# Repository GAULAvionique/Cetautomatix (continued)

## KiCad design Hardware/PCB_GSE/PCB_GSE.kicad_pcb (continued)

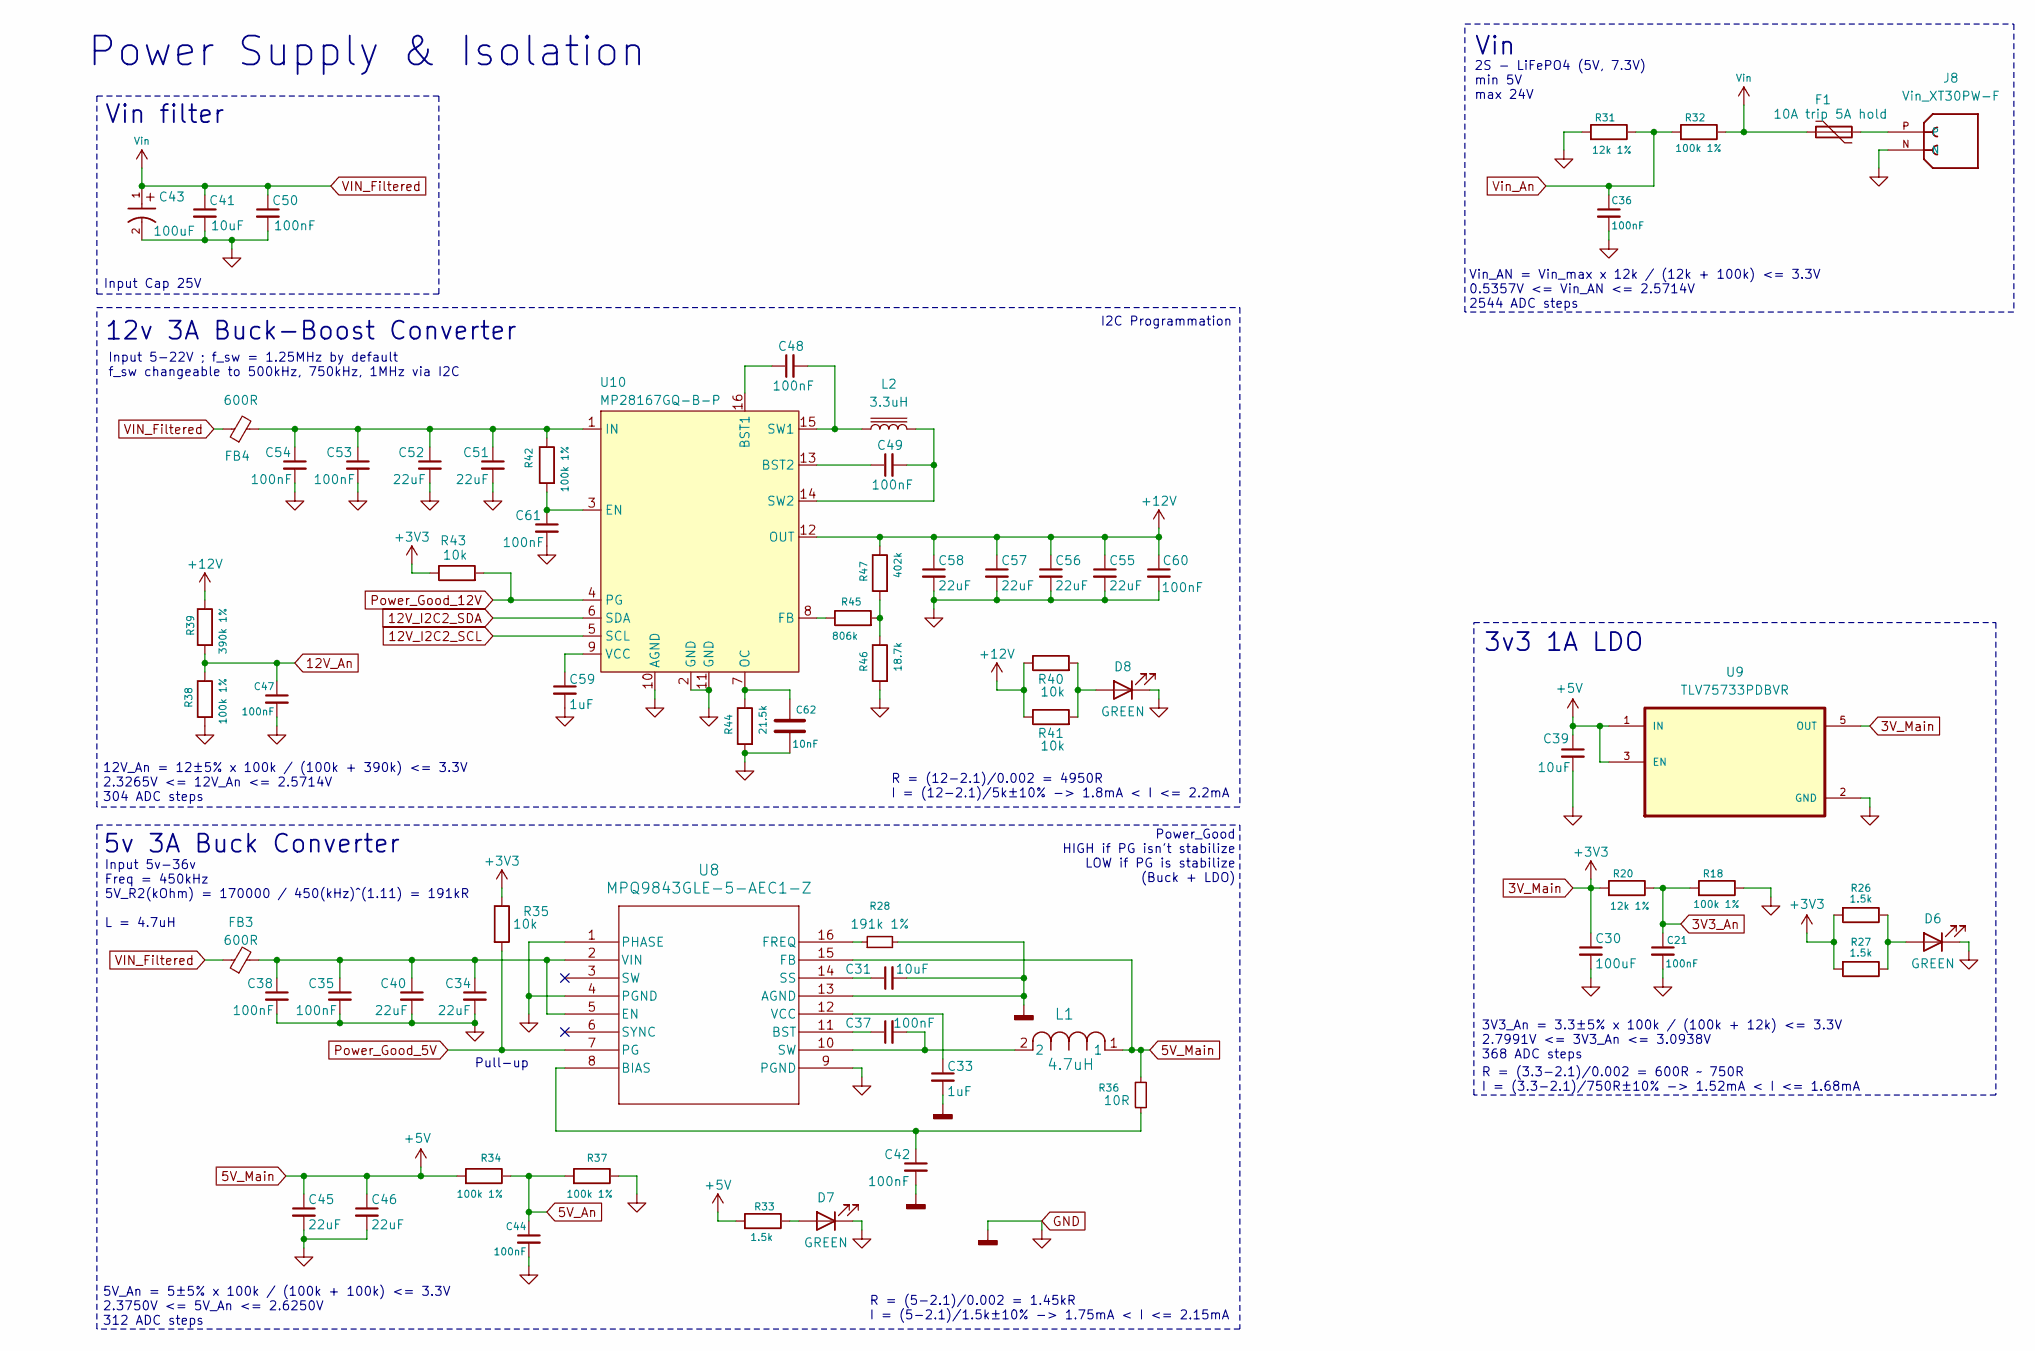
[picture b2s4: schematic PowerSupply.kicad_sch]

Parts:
C21, C35, C36, C37, C38, C42, C44, C47, C48, C49, C50, C53, C54, C60, C61: 100nF; C_0603_1608Metric; Manufacturer_Part_Number C0603C104K3RACTU; DigiKey_Part_Number 399-C0603C104K3RACTUCT-ND
C30: 100uF; C_1210_3225Metric; Manufacturer_Part_Number EMK325ABJ107MM-P; DigiKey_Part_Number 587-5426-1-ND
C31, C39, C41: 10uF; C_0805_2012Metric; Manufacturer_Part_Number CL21A106KAYNNNE; DigiKey_Part_Number 1276-2891-1-ND
C33, C59: 1uF; C_0805_2012Metric; Manufacturer_Part_Number CL21B105KBFNNNE; DigiKey_Part_Number 1276-1029-1-ND
C34, C40, C45, C46, C51, C52, C55, C56, C57, C58: 22uF; C_0805_2012Metric; Manufacturer_Part_Number C2012X5R1V226M125AC; DigiKey_Part_Number 445-14428-1-ND
C43: 100uF; U2-K_NCH; Manufacturer_Part_Number UCL1E101MCL1GS; DigiKey_Part_Number 493-3937-1-ND
C62: 10nF; C_0805_2012Metric; Manufacturer_Part_Number CL21B103KAANNNC; DigiKey_Part_Number 1276-2434-1-ND
D6, D7, D8: GREEN; LED_QBLP601-AG15; Manufacturer_Part_Number QBLP601-AG15; DigiKey_Part_Number 1516-QBLP601-AG15CT-ND
F1: 10A trip 5A hold; Fuse_2920_7451Metric; Manufacturer_Part_Number 2920L500/24SLDR; DigiKey_Part_Number 18-2920L500/24SLDRCT-ND
FB3, FB4: 600R; L_1210_3225Metric; Manufacturer_Part_Number FBMH3225HM601NT; DigiKey_Part_Number 587-1755-1-ND
J8: Vin_XT30PW-F; XT30PW-F; PARTREV 1.2
L1: 4.7uH; IND_PA4342_PUL; Manufacturer_Part_Number PA4342.472NLT; Digikey 553-3001-1-ND
L2: 3.3uH; MPL-AL6050-3R3; Manufacturer_Part_Number MPL-AL6050-3R3; DigiKey_Part_Number 1589-MPL-AL6050-3R3CT-ND
R18, R32, R34, R37, R38, R42: 100k 1%; R_0805_2012Metric; Manufacturer_Part_Number RC0805FR-07100KL; DigiKey_Part_Number 311-100KCRCT-ND
R20, R31: 12k 1%; R_0805_2012Metric; Manufacturer_Part_Number RC0805FR-0712KL; DigiKey_Part_Number 311-12.0KCRCT-ND
R26, R27, R33: 1.5k; R_0805_2012Metric; Manufacturer_Part_Number RC0805FR-071K5L; DigiKey_Part_Number 311-1.50KCRCT-ND
R28: 191k 1%; R_0805_2012Metric; Manufacturer_Part_Number RC0805FR-07191KL; DigiKey_Part_Number 311-191KCRCT-ND
R35, R40, R41, R43: 10k; R_0805_2012Metric; Manufacturer_Part_Number CRCW080510K0FKEA; DigiKey_Part_Number 541-10.0KCCT-ND
R36: 10R; R_0805_2012Metric; Manufacturer_Part_Number RC0805FR-0710RL; DigiKey_Part_Number 311-10.0CRCT-ND
R39: 390k 1%; R_0805_2012Metric; Manufacturer_Part_Number RK73H2ATTD3903F; DigiKey_Part_Number 2019-RK73H2ATTD3903FCT-ND
R44: 21.5k; R_0805_2012Metric; Manufacturer_Part_Number CRCW080521K5FKEA; DigiKey_Part_Number 541-21.5KCCT-ND
R45: 806k; R_0805_2012Metric; Manufacturer_Part_Number RC0805FR-07806KL; DigiKey_Part_Number 311-806KCRCT-ND
R46: 18.7k; R_0805_2012Metric; Manufacturer_Part_Number RMCF0805FT18K7; DigiKey_Part_Number RMCF0805FT18K7CT-ND
R47: 402k; R_0805_2012Metric; Manufacturer_Part_Number RC0805FR-07402KL; DigiKey_Part_Number 311-402KCRCT-ND
U8: MPQ9843GLE-5-AEC1-Z; MPQ9843GLE_5_AEC1_Z; Manufacturer_Part_Number MPQ9843GLE-5-AEC1-Z; DigiKey_Part_Number 1589-MPQ9843GLE-5-AEC1-ZCT-ND
U9: TLV75733PDBVR; SOT-23-5; Manufacturer_Part_Number TLV75733PDBVR; DigiKey_Part_Number 296-50414-1-ND
U10: MP28167GQ-B-P; QFN-16_MP28167_MNP; Manufacturer_Part_Number MP28167GQ-B-P; DigiKey_Part_Number 1589-MP28167GQ-B-PCT-ND

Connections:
3V3_An: C21.1, R18.2, R20.1; also elsewhere on the board
3V_Main: C30.1, R20.2, R26.2, R27.2, R35.1, R43.1, U9.5 (OUT); also elsewhere on the board
5V_An: C44.1, R34.1, R37.2; also elsewhere on the board
5V_Main: C39.1, C45.1, C46.1, L1.1, R33.2, R34.2, R36.1, U8.15 (FB), U9.1 (IN), U9.3 (EN); also elsewhere on the board
12V_An: C47.1, R38.1, R39.2; also elsewhere on the board
12V_I2C2_SCL: U10.5 (SCL); also elsewhere on the board
12V_I2C2_SDA: U10.6 (SDA); also elsewhere on the board
GND: C21.2, C30.2, C31.2, C33.2, C34.2, C35.2, C36.2, C38.2, C39.2, C40.2, C41.2, C42.2, C43.2, C44.2, C45.2, C46.2, C47.2, C50.2, C51.2, C52.2, C53.2, C54.2, C55.2, C56.2, C57.2, C58.2, C59.2, C60.2, C61.2, C62.1, D6.1 (K), D7.1 (K), D8.1 (K), J8.N, R18.1, R28.2, R31.2, R37.1, R38.2, R44.2, R46.2, U8.1 (PHASE), U8.4 (PGND), U8.9 (PGND), U8.13 (AGND), U9.2 (GND), U10.2 (GND), U10.10 (AGND), U10.11 (GND); also elsewhere on the board
unnamed: C37.2, L1.2, U8.10 (SW)
unnamed: D6.2 (A), R26.1, R27.1
unnamed: D7.2 (A), R33.1
unnamed: D8.2 (A), R40.2, R41.2
unnamed: F1.2, J8.P
unnamed: R45.2, R46.1, R47.2
unnamed: C42.1, R36.2, U8.8 (BIAS)
unnamed: C37.1, U8.11 (BST)
unnamed: C34.1, C35.1, C38.1, C40.1, FB3.2, U8.2 (VIN), U8.5 (EN)
unnamed: R28.1, U8.16 (FREQ)
unnamed: C31.1, U8.14 (SS)
unnamed: C33.1, U8.12 (VCC)
unnamed: C48.1, U10.16 (BST1)
unnamed: C49.1, U10.13 (BST2)
unnamed: C61.1, R42.2, U10.3 (EN)
unnamed: R45.1, U10.8 (FB)
unnamed: C51.1, C52.1, C53.1, C54.1, FB4.2, R42.1, U10.1 (IN)
unnamed: C62.2, R44.1, U10.7 (OC)
unnamed: C48.2, L2.1, U10.15 (SW1)
unnamed: C49.2, L2.2, U10.14 (SW2)
unnamed: C59.1, U10.9 (VCC)
Power_Good_5V: R35.2, U8.7 (PG); also elsewhere on the board
Power_Good_12V: R43.2, U10.4 (PG); also elsewhere on the board
VIN_Filtered: C41.1, C43.1, C50.1, F1.1, FB3.1, FB4.1, R32.1; also elsewhere on the board
Vin_An: C36.1, R31.1, R32.2; also elsewhere on the board
Vin_Valve: C55.1, C56.1, C57.1, C58.1, C60.1, R39.1, R40.1, R41.1, R47.1, U10.12 (OUT); also elsewhere on the board

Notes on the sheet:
I2C Programmation
R = (5-2.1)/0.002 = 1.45kR I = (5-2.1)/1.5k±10% -> 1.75mA < I <= 2.15mA
12v 3A Buck-Boost Converter
Vin
Input Cap 25V
Vin filter
Vin_AN = Vin_max x 12k / (12k + 100k) <= 3.3V 0.5357V <= Vin_AN <= 2.5714V 2544 ADC steps
Power Supply & Isolation
Pull-up
R = (3.3-2.1)/0.002 = 600R ~ 750R I = (3.3-2.1)/750R±10% -> 1.52mA < I <= 1.68mA
5v 3A Buck Converter
Input 5v-36v Freq = 450kHz 5V_R2(kOhm) = 170000 / 450(kHz)^(1.11) = 191kR L = 4.7uH
3v3 1A LDO
2S - LiFePO4 (5V, 7.3V) min 5V max 24V
5V_An = 5±5% x 100k / (100k + 100k) <= 3.3V 2.3750V <= 5V_An <= 2.6250V 312 ADC steps
R = (12-2.1)/0.002 = 4950R I = (12-2.1)/5k±10% -> 1.8mA < I <= 2.2mA
Input 5-22V ; f_sw = 1.25MHz by default f_sw changeable to 500kHz, 750kHz, 1MHz via I2C
12V_An = 12±5% x 100k / (100k + 390k) <= 3.3V 2.3265V <= 12V_An <= 2.5714V 304 ADC steps
3V3_An = 3.3±5% x 100k / (100k + 12k) <= 3.3V 2.7991V <= 3V3_An <= 3.0938V 368 ADC steps
Power_Good HIGH if PG isn't stabilize LOW if PG is stabilize (Buck + LDO)

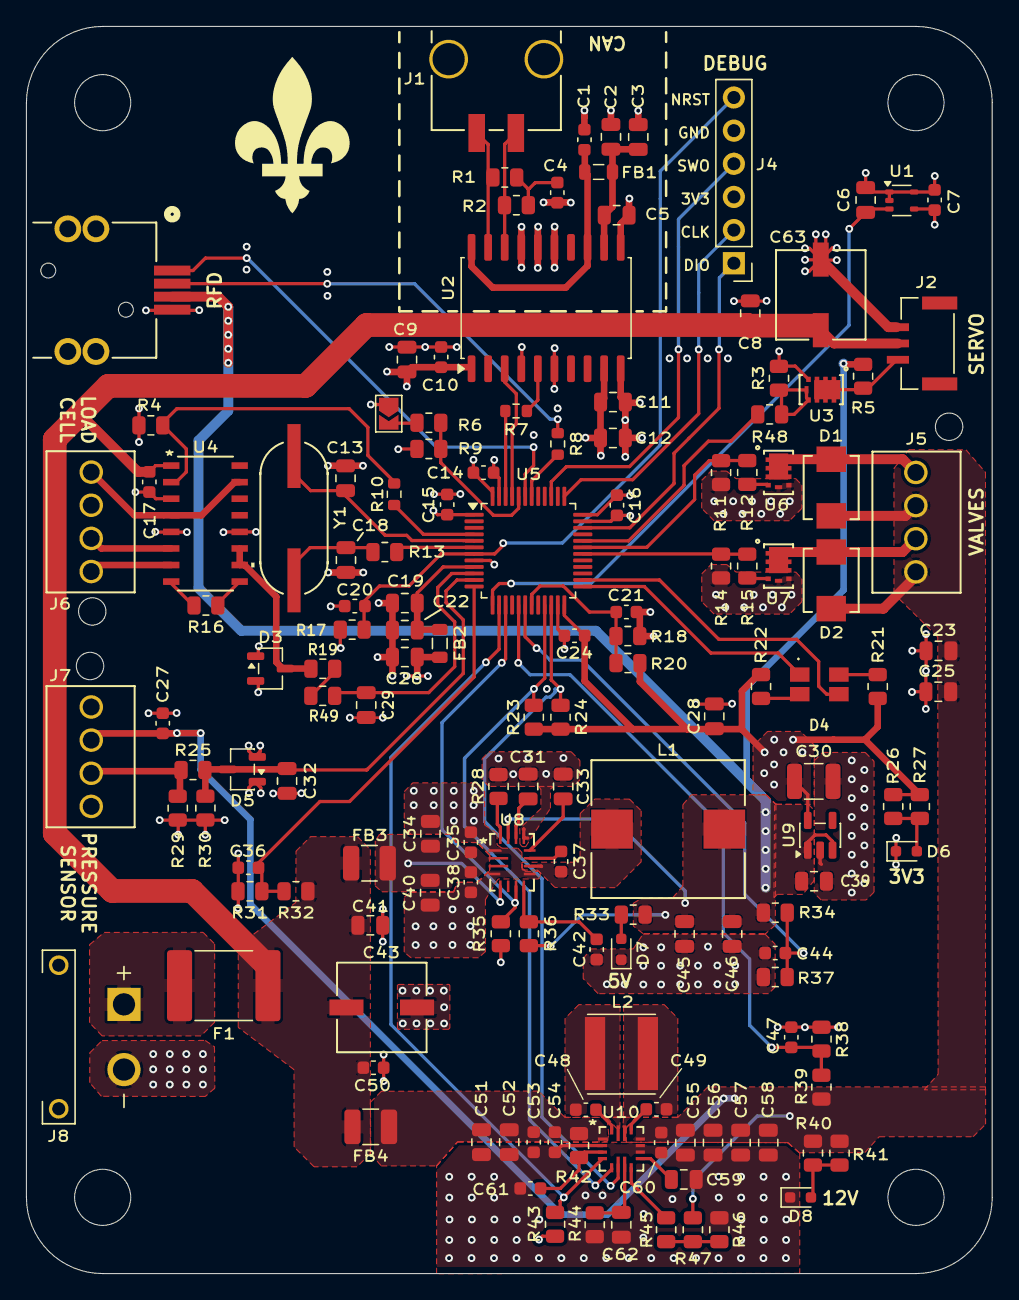
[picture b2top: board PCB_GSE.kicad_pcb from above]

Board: 4 copper layers, 74.0 x 95.6 mm, 151 parts (0 on the bottom side), 82 nets.

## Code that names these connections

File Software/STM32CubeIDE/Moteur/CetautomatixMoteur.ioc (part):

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Mcu.Name=STM32F103C(8-B)Tx
Mcu.Package=LQFP48
Mcu.UserName=STM32F103CBTx
PA0-WKUP.GPIOParameters=GPIO_Label
PA0-WKUP.GPIO_Label=Pressure_An
PA0-WKUP.Signal=ADCx_IN0
PA1.GPIOParameters=GPIO_Label
PA1.GPIO_Label=LCell_An
PA1.Signal=ADCx_IN1
PA10.GPIOParameters=GPIO_Label
PA10.GPIO_Label=Servo2_PWM
PA10.Signal=S_TIM1_CH3
PA11.GPIOParameters=GPIO_Label
PA11.GPIO_Label=Servo1_PWM
PA11.Signal=S_TIM1_CH4
PA12.GPIOParameters=GPIO_Label
PA12.GPIO_Label=Servo2_Open
PA12.Signal=GPIO_Input
PA13.GPIOParameters=GPIO_Label
PA13.GPIO_Label=SYS_SWDIO
PA13.Mode=Trace_Asynchronous_SW
PA13.Signal=SYS_JTMS-SWDIO
PA14.GPIOParameters=GPIO_Label
PA14.GPIO_Label=SYS_SWCLK
PA14.Mode=Trace_Asynchronous_SW
PA14.Signal=SYS_JTCK-SWCLK
PA15.GPIOParameters=GPIO_Label
PA15.GPIO_Label=Servo2_Close
PA15.Signal=GPIO_Input
PA2.GPIOParameters=GPIO_Label
PA2.GPIO_Label=Temp_An
PA2.Signal=ADCx_IN2
PA3.GPIOParameters=GPIO_Label
PA3.GPIO_Label=Sense_1
PA3.Signal=ADCx_IN3
PA4.GPIOParameters=GPIO_Label
PA4.GPIO_Label=Sense_2
PA4.Signal=ADCx_IN4
PA5.GPIOParameters=GPIO_Label
PA5.GPIO_Label=PA_An
PA5.Signal=ADCx_IN5
PA6.GPIOParameters=GPIO_Label
PA6.GPIO_Label=Vin_An
PA6.Signal=ADCx_IN6
PA7.GPIOParameters=GPIO_Label
PA7.GPIO_Label=Vswagelok_An
PA7.Signal=ADCx_IN7
PA8.GPIOParameters=GPIO_Label
PA8.GPIO_Label=Servo4_PWM
PA8.Signal=S_TIM1_CH1
PA9.GPIOParameters=GPIO_Label
PA9.GPIO_Label=Servo3_PWM
PA9.Signal=S_TIM1_CH2
PB0.GPIOParameters=GPIO_Label
PB0.GPIO_Label=V3_An
PB0.Signal=ADCx_IN8
PB1.GPIOParameters=GPIO_Label
PB1.GPIO_Label=Fire_1
PB1.Signal=GPIO_Output
PB10.GPIOParameters=GPIO_Label
PB10.GPIO_Label=Pyros_Arm
PB10.Signal=GPIO_Output
PB12.GPIOParameters=GPIO_Label
PB12.GPIO_Label=Servo4_Close
PB12.Signal=GPIO_Input
PB13.GPIOParameters=GPIO_Label
PB13.GPIO_Label=Servo4_Open
PB13.Signal=GPIO_Input
PB14.GPIOParameters=GPIO_Label
PB14.GPIO_Label=Servo3_Close
PB14.Signal=GPIO_Input
PB15.GPIOParameters=GPIO_Label
PB15.GPIO_Label=Servo3_Open
PB15.Signal=GPIO_Input
PB2.GPIOParameters=GPIO_Label
PB2.GPIO_Label=Fire_2
PB2.Signal=GPIO_Output
PB3.GPIOParameters=GPIO_Label
PB3.GPIO_Label=SYS_SWO
PB3.Mode=Trace_Asynchronous_SW
PB3.Signal=SYS_JTDO-TRACESWO
PB4.GPIOParameters=GPIO_Label
PB4.GPIO_Label=Servo1_Open
PB4.Signal=GPIO_Input
PB5.GPIOParameters=GPIO_Label
PB5.GPIO_Label=Servo1_Close
PB5.Signal=GPIO_Input
PB6.GPIOParameters=GPIO_Label
PB6.GPIO_Label=CriticalLED_R
PB6.Signal=GPIO_Output
PB7.GPIOParameters=GPIO_Label
PB7.GPIO_Label=CriticalLED_G
PB7.Signal=GPIO_Output
PB8.GPIOParameters=GPIO_Label
PB8.GPIO_Label=ISO_CAN_RXD
PB8.Mode=CAN_Activate
PB8.Signal=CAN_RX
PB9.GPIOParameters=GPIO_Label
PB9.GPIO_Label=ISO_CAN_TXD
PB9.Mode=CAN_Activate
PB9.Signal=CAN_TX
PC15-OSC32_OUT.GPIOParameters=GPIO_Label
PC15-OSC32_OUT.GPIO_Label=LCell_Sleep
PC15-OSC32_OUT.Signal=GPIO_Output
PD0-OSC_IN.GPIOParameters=GPIO_Label
PD0-OSC_IN.GPIO_Label=OSC_IN
PD0-OSC_IN.Mode=HSE-External-Oscillator
PD0-OSC_IN.Signal=RCC_OSC_IN
PD1-OSC_OUT.GPIOParameters=GPIO_Label
PD1-OSC_OUT.GPIO_Label=OSC_OUT
PD1-OSC_OUT.Mode=HSE-External-Oscillator
PD1-OSC_OUT.Signal=RCC_OSC_OUT
board=custom

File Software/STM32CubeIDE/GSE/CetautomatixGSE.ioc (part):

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Mcu.Name=STM32F103C(8-B)Tx
Mcu.Package=LQFP48
Mcu.UserName=STM32F103CBTx
PA0-WKUP.GPIOParameters=GPIO_Label
PA0-WKUP.GPIO_Label=LCell_An
PA0-WKUP.Signal=ADCx_IN0
PA1.GPIOParameters=GPIO_Label
PA1.GPIO_Label=Pressure_An
PA1.Signal=ADCx_IN1
PA10.GPIOParameters=GPIO_Label
PA10.GPIO_Label=Valve2_Open
PA10.Signal=GPIO_Output
PA11.GPIOParameters=GPIO_Label
PA11.GPIO_Label=Servo3_PWM
PA11.Signal=S_TIM1_CH4
PA13.GPIOParameters=GPIO_Label
PA13.GPIO_Label=SYS_SWDIO
PA13.Mode=Trace_Asynchronous_SW
PA13.Signal=SYS_JTMS-SWDIO
PA14.GPIOParameters=GPIO_Label
PA14.GPIO_Label=SYS_SWCLK
PA14.Mode=Trace_Asynchronous_SW
PA14.Signal=SYS_JTCK-SWCLK
PA2.GPIOParameters=GPIO_Label
PA2.GPIO_Label=Vin_An
PA2.Signal=ADCx_IN2
PA3.GPIOParameters=GPIO_Label
PA3.GPIO_Label=Temp_An
PA3.Signal=ADCx_IN3
PA4.GPIOParameters=GPIO_Label
PA4.GPIO_Label=Power_Good_12V
PA4.Signal=ADCx_IN4
PA5.GPIOParameters=GPIO_Label
PA5.GPIO_Label=Power_Good_5V
PA5.Signal=GPIO_Input
PA7.GPIOParameters=GPIO_Label
PA7.GPIO_Label=V12_An
PA7.Signal=ADCx_IN7
PA9.GPIOParameters=GPIO_Label
PA9.GPIO_Label=Valve1_Open
PA9.Signal=GPIO_Output
PB0.GPIOParameters=GPIO_Label
PB0.GPIO_Label=V5_An
PB0.Signal=GPIO_Input
PB1.GPIOParameters=GPIO_Label
PB1.GPIO_Label=V3_An
PB1.Signal=ADCx_IN9
PB10.GPIOParameters=GPIO_Label
PB10.GPIO_Label=V12_I2C2_SCL
PB10.Mode=I2C
PB10.Signal=I2C2_SCL
PB11.GPIOParameters=GPIO_Label
PB11.GPIO_Label=V12_I2C2_SDA
PB11.Mode=I2C
PB11.Signal=I2C2_SDA
PB12.GPIOParameters=GPIO_Label
PB12.GPIO_Label=CriticalLED_R
PB12.Signal=GPIO_Output
PB13.GPIOParameters=GPIO_Label
PB13.GPIO_Label=CriticalLED_G
PB13.Signal=GPIO_Output
PB3.GPIOParameters=GPIO_Label
PB3.GPIO_Label=SYS_SWO
PB3.Mode=Trace_Asynchronous_SW
PB3.Signal=SYS_JTDO-TRACESWO
PB6.GPIOParameters=GPIO_Label
PB6.GPIO_Label=RFD_USART1_TX
PB6.Mode=Asynchronous
PB6.Signal=USART1_TX
PB7.GPIOParameters=GPIO_Label
PB7.GPIO_Label=RFD_USART1_RX
PB7.Mode=Asynchronous
PB7.Signal=USART1_RX
PB8.GPIOParameters=GPIO_Label
PB8.GPIO_Label=ISO_CAN_RXD
PB8.Mode=CAN_Activate
PB8.Signal=CAN_RX
PB9.GPIOParameters=GPIO_Label
PB9.GPIO_Label=ISO_CAN_TXD
PB9.Mode=CAN_Activate
PB9.Signal=CAN_TX
PC15-OSC32_OUT.GPIOParameters=GPIO_Label
PC15-OSC32_OUT.GPIO_Label=LCell_Sleep
PC15-OSC32_OUT.Signal=GPIO_Output
PD0-OSC_IN.GPIOParameters=GPIO_Label
PD0-OSC_IN.GPIO_Label=OSC_IN
PD0-OSC_IN.Mode=HSE-External-Oscillator
PD0-OSC_IN.Signal=RCC_OSC_IN
PD1-OSC_OUT.GPIOParameters=GPIO_Label
PD1-OSC_OUT.GPIO_Label=OSC_OUT
PD1-OSC_OUT.Mode=HSE-External-Oscillator
PD1-OSC_OUT.Signal=RCC_OSC_OUT
RCC.SYSCLKFreq_VALUE=72000000
RCC.SYSCLKSource=RCC_SYSCLKSOURCE_PLLCLK
board=custom

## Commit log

2025-09-30 Fix: Rename NautilPCB to Cétaumotorix in Schemas.md
2025-09-30 Fix: typo in title from 'Cétaumotorix' to 'Cétautomatix'
2025-10-25 création projets kicad
2025-11-06 Début schéma moteurs
2025-11-09 fix: repo
2025-11-10 tx de rfd et can, pas encore tester, donc d'autres modifications à venir
2025-11-10 Revert "tx de rfd et can, pas encore tester, donc d'autres modifications à venir"
    This reverts commit 7740cc68a9cf953570aa067b4b73ca5d330767ca.
2025-11-20 feat: Add Showcase.md
2025-11-20 feat: add diagram systems
2025-11-20 fix: Delete Documentation/NautilPCB.png
2025-11-20 fix: Update image in Showcase documentation
2025-11-20 fix: Delete Documentation/Diagram_Cetaumatix.png
2025-12-27 Manque supply, pyro et finition (découplage etc)
2025-12-27 wip: remove unnecessary components
2025-12-27 wip: change 4 pyros -> 2 pyros
2026-01-05 génération du code pour le CAN
    ajout des pines dans STM32CubeMX et génération du code.
2026-01-05 nouvelle génération de code
2026-01-07 on recommence
2026-01-11 trames de commande
2026-01-11 modification du main
2026-01-11 avancement général.
2026-01-11 version documenté un peux plus
2026-01-12 fix: power supply + add LED RG + add mounting holes + change 6pins header SWD connector + pyros
2026-01-13 fix: resistors + capacitances power supply
2026-01-14 avancement code
2026-01-14 Added LDO, INA125, sensors
2026-01-14 finis pression, loadcell, temperature
2026-01-15 fichier des composants
    téléchargement des fichiers des divers composant
2026-01-15 ajout des composant (vérification des pin à faire !!!!!!!!!!!!!!!!!)
2026-01-15 modification des symbole
2026-01-15 modèle 3d et foot_print
2026-01-15 un espace de retiré
2026-01-15 modif mineure (pull-up, découplage)
2026-01-16 fix: pyros resistors + typos +
2026-01-17 fix: resistance ratios + typos
2026-01-17 repo: add gitignore
2026-01-17 repo: apply gitignore rules and untrack ignored files
2026-01-17 repo: change directories + rename branches
2026-01-17 feat: add stm32 project
2026-01-17 feat: setup stm32 project + mapping + add led LDO
2026-01-17 fix: minor corrections aux servos avant souper
2026-01-18 fix: LDO SHDN + complete stm32cubeide mapping (kicad missing) + add CAN in binary signal (connector missing)
2026-01-18 rapport générer pour les connecteurs du stm32
2026-01-18 fix: readd mapping changes (save)
2026-01-18 wip : pin mapping on STM32 and limit switch circuit
2026-01-18 feat: add extend ios + fix mapping kicad + add transmitter resistors
2026-01-18 fix: LDO 5V SHDN + REFs (missing) + change EN valves controller connection + fix intrumental ampliop + add pull-down to sleep pins
2026-01-19 Calculs gains, filtre rc
2026-01-19 wip : minor corrections and fix footprints except connectors
2026-01-19 fix: symbols refactorisation (footprint missing)
2026-01-19 restoration des descriptions et des informations/link
2026-01-19 wip : done all footprints
2026-01-19 wip : add final footprint to lib and start pcb
2026-01-19 changement de fichier de symbole pour un avec plus de modèle et ajout du deuxième fichier au cas où il le symbole à été mis dedans.
2026-01-19 tout les footprint son prêt
2026-01-19 board size et exploration
2026-01-20 début alim
2026-01-20 Composant 3d
    Sauf une inductance
2026-01-20 Version avec vraiment les compo 3d
2026-01-20 Layout Alim 3.3V + pression et loadcell
2026-01-20 del save
2026-01-20 un peux de regroupement sans faire exactement le layout
2026-01-20 chore: Update copyright in LICENSE file
2026-01-20 chore: change copyright year to 2026
    Updated copyright year in the LICENSE file.
2026-01-20 wip: layout circuits Pyro
2026-01-20 wip: début CAN Layout
2026-01-21 wip: fin layout CAN et interface servo
2026-01-21 fix(stm32): update pin servo1 <-> servo2
2026-01-21 wip: fin des circuits sauf ceux du STM
2026-01-21 wip: layout presque fini (decoup stm32 restant)
2026-01-21 wip: nouveaux connecteurs et espace pour ceux-ci
2026-01-22 wip: arrangement connecteurs et modeles 3D
2026-01-22 wip: finis layout, DRIP MAXIMALE
2026-01-22 ajout des composants dans GSE
2026-01-22 wip: début routing
2026-01-22 hierarchisation des feuille
2026-01-23 un peux d'avancement (brouillon)
2026-01-23 wip: routing (suite)
2026-01-23 feat: copy all existing schematics in gse project + add missing components + fix voltage divider for 3S + create gse project and seperate stm32 project + add missing resistors motor
2026-01-24 wip: routing sys et limit switches
2026-01-24 fix: typos
2026-01-25 feat: add 12V buck converter + inductance symbol/footprint
2026-01-26 feat: finish 12V-3A buck converter
2026-01-26 fix: add ferritbead + remove typos
2026-01-26 fix: stm32 project + modified 12v buck symbol
2026-01-26 fix: change Schottky diode 12v buck
2026-01-26 feat: add valve control + needed components
2026-01-26 feat: add extended ios + add stm32 project extended ios +
2026-01-27 chore: fix gitignore
    Removed version directories from .gitignore
2026-01-27 feat: change buck 3v3 1A ->5V 3A to 3.3V 1A cascade LDO + add symbol/footprint
2026-01-29 wip: finit routing servo et limit switch, début pyro
2026-01-29 wip: pyro suite
2026-01-30 wip: routing, bientot plane d'alim!
2026-01-30 wip: reste plane
2026-02-01 refactor: merge emile + main branches
2026-02-01 fix: labels
2026-02-01 fix: decoupling 3v3 missing
2026-02-01 wip : Reduce BOM and fill all datasheet, digikey and MPN
2026-02-02 wip: begining layout
2026-02-02 wip: change in trace width
2026-02-02 wip: trace width
2026-02-04 wip: changement trace width et début GND Via
2026-02-04 wip: via
2026-02-05 wip: GND vias et power polygon patching
2026-02-05 wip: plane and 5V
2026-02-06 feat: add 8MHz crystal, fix extended ios, fix pinout with HSE, update smt32 project, begin layout edge
2026-02-06 feat(moteur): add 8MHz crystal (only schematic), fix ERC, update stm32 project, remove extend ios
2026-02-07 chore: Change buck 12v
2026-02-08 fix(GSE & Moteur): change Vin adc divider
2026-02-14 change 12V buck to 12V buck-boost
2026-02-14 wip : add BOM for 12V buck-boost
2026-02-14 wip : subsystems layout
2026-02-15 wip(gse): edge
2026-02-15 wip(gse): begin layout
2026-02-15 wip : finished layout and routing of powersupplys
2026-02-15 wip : routing local circuits and power planes
2026-02-15 fix(gse): stm32cubeide project import trames struct
2026-02-15 fix(gse & moteur): mapping + routing, remove CAN_ISO_IN/OUT
2026-02-16 wip : Done routing
2026-03-02 wip(GSE): ajout des fichiers dans stm32CubeIDE
2026-03-02 fix : replace valve 3 with servomotor on schematic
2026-03-02 fix : replace Pressure sensor amplification circuit with new voltage divider circuit
2026-03-02 fix : routing des modifications Servo et capteur pression
2026-03-03 fix : done silkscreen and finition
2026-03-03 wip: Cristal et modifs routing
2026-03-04 wip: separation GND et modif schéma pression
2026-03-04 wip: new pressure et fix alim
2026-03-04 wip : work on silkscreen and add all info to BOM
2026-03-04 wip : reorder refdes and fix footprints
2026-03-05 fix(gse): Vin servo
2026-03-05 fix(moteur + gse): gnd not connected for pressure sensor + seperate alim pressure sensor for motor pcb
2026-03-05 fix(gse): change Servo3_PWM -> TIM1_CH2, change Valve1/2_Open pin
2026-03-05 fix(moteur): remove Pressure_Sleep pin to stm32cubeide project
2026-03-05 fix : cap electrolytique servo
2026-03-05 wip première version du CAN généraliser
2026-03-05 wip: new alim, power plane and pin changes
2026-03-05 wip(moteur): traces
2026-03-06 wip: FINI DE CONNECTER LES NETS
2026-03-06 wip: erreurs de DRC corrigées
2026-03-06 fix : finished silkscreen finition
2026-03-06 add unit test and Remove Debug build folder from repository
2026-03-06 wip (update)
2026-03-06 wip (prepa compatibilité)
2026-03-07 fix: silkscreen green<->black + fix silkscreen + connect shield to gnd in pressure sensor + fix/add doc
2026-03-07 fix(moteur + gse): move xt30 to border + fix silkscreen + connect shield to gnd in pressure sensor + remake rounded corners + fix/add doc
2026-03-07 wip(moteur): reimport SI7617DN-T1-GE3 footprint + fix pads
2026-03-07 wip(moteur + gse): fix silkscreen + traces + polygons
2026-03-07 wip(moteur): add jack connector + fix dump valve
2026-03-07 Fix : connect all nets and fix dump valve kill
2026-03-07 Fix : servo side connectors
2026-03-08 fix : add polyfuses and fix 90 deg servo connectors
2026-03-08 fix : BOM errors, change cutoff freq for moteur, minor fixes for GSE
2026-03-08 chore: clean up the pcb and optimize some routings
2026-03-08 fix(gse): Vin trace
2026-03-09 tests fonctionnels
2026-03-09 transition vers vscode
2026-03-09 clean
2026-03-09 feature : Done v1 and send to fab
2026-03-09 mise-à-jours
2026-03-09 (wip) mise à jours de la documentation
2026-03-09 fix(gse): change Swahelok S model -> Swagelok A model (adaptable) + 100R -> 100R 1% + silkscreen
2026-03-09 fix(moteur): change Swahelok S model -> Swagelok A model (adaptable) + 100R -> 100R 1% + silkscreen
2026-03-10 fix(moteur): mosfet pyros pads
2026-03-10 fabrication v2
2026-03-10 trames d'etats
2026-03-11 remove trame from here
2026-03-15 refactor: trame -> GSE
    main loop missing + received behavior missing
2026-03-15 feat!: add uart dma + ring buffer + uart interrupt + can rx interrupt + add logs in gse->sas frame & motor->gse frame + refactor can in seperated files + add clock ioc configuratio + add ioc uart + c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
2026-03-16 fix!(gse): can 9 bytes receptions + use ring buffer
2026-03-16 fix(gse): thrut_loadcell + ring buffer optimisation + fix 9bytes gse<-motor pack + add uart tx dma + add verifs
2026-03-16 fix(gse): bad return UART_DMA_Start
2026-03-16 feat(gse): add crtiticalLED + begin buck 12v
2026-03-16 feat: add mp28167 12v buck
2026-03-17 feat: add adc dual reading with extend dma + add converted pression/load cell + add tare functions for pression/load cell + move into lowlevel folder
2026-03-17 chore: add typo frame
2026-03-17 refactor: GAUL_Drivers->GAUL/Drivers
2026-03-19 feat!: add data in structs gse
2026-03-23 feat(gse): add servo/solenoid driver + fix adc_dual init
2026-03-23 fix(gse): fix trame typo
2026-03-23 chore: revert to commit 1d0c063
2026-03-23 chore: remove trame project from Overview branch
2026-03-23 Create GAUL folder
2026-03-23 chore(overview): readd lost files
2026-03-23 chore(overview): revision protocole
    Updated the protocol for armament, adding details for Ground Support Equipment (GSE) and Rocket components, including device states during various phases.
2026-03-24 feat(gse): add watchdog driver
